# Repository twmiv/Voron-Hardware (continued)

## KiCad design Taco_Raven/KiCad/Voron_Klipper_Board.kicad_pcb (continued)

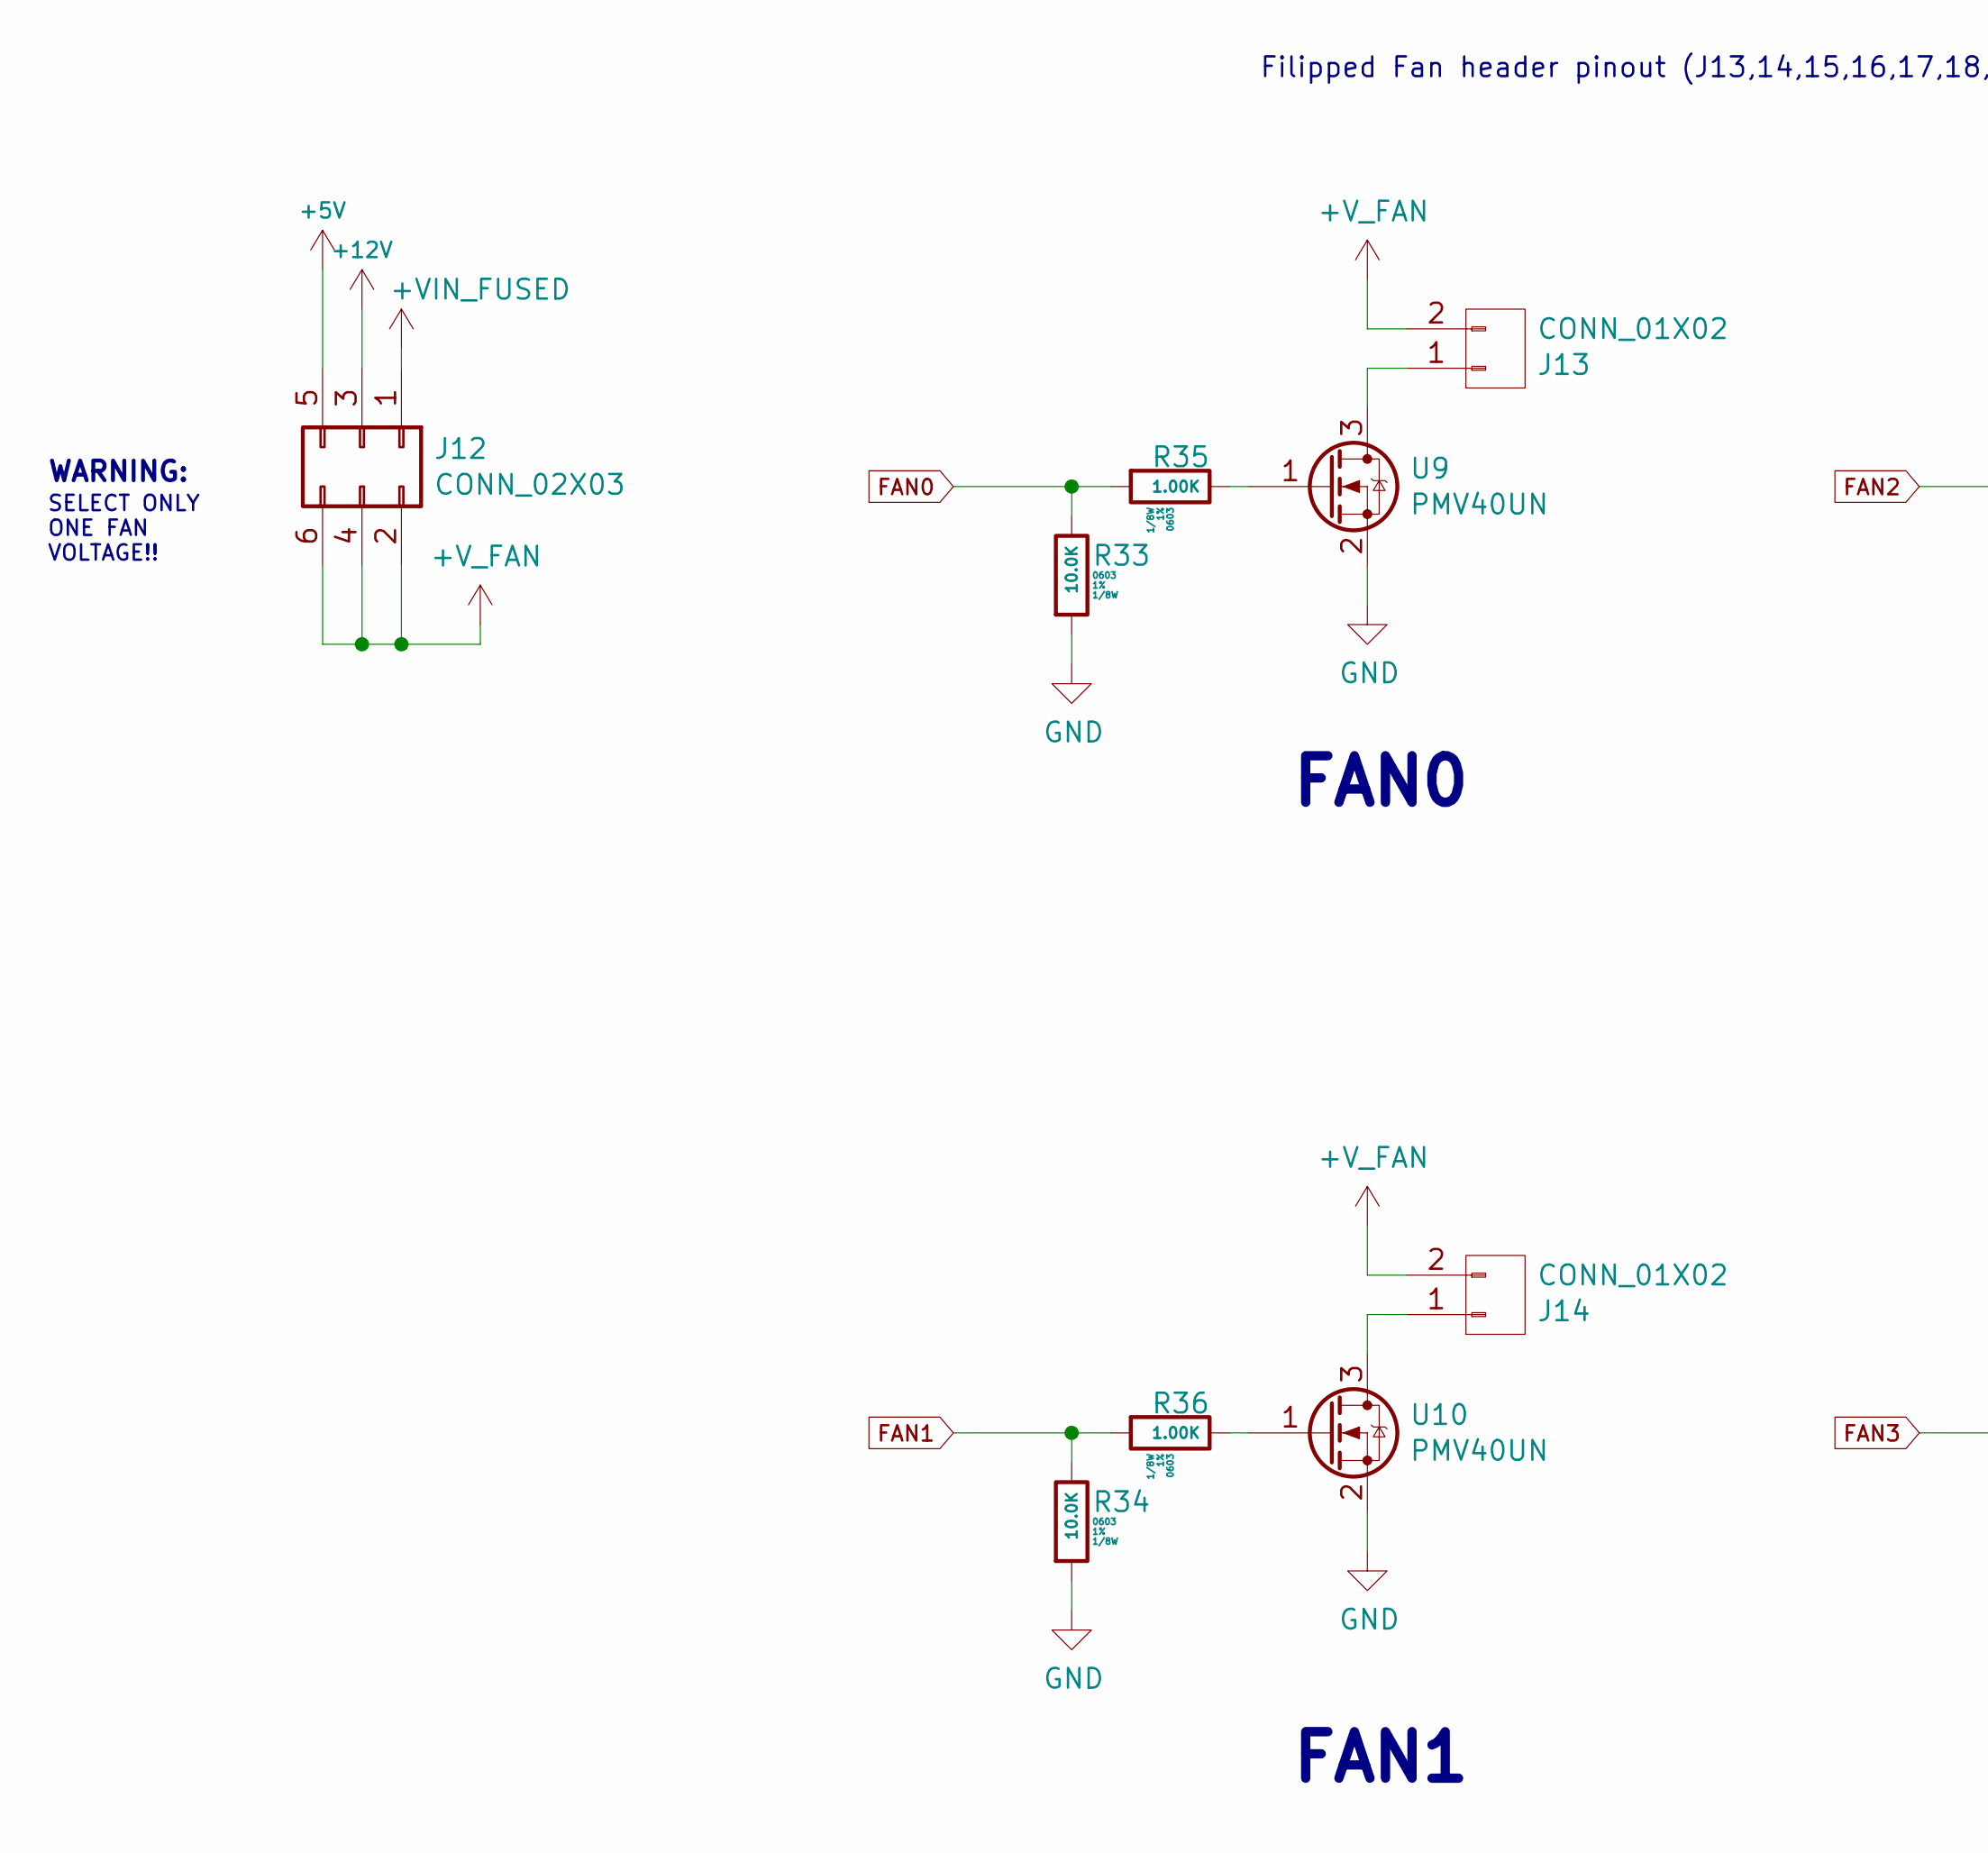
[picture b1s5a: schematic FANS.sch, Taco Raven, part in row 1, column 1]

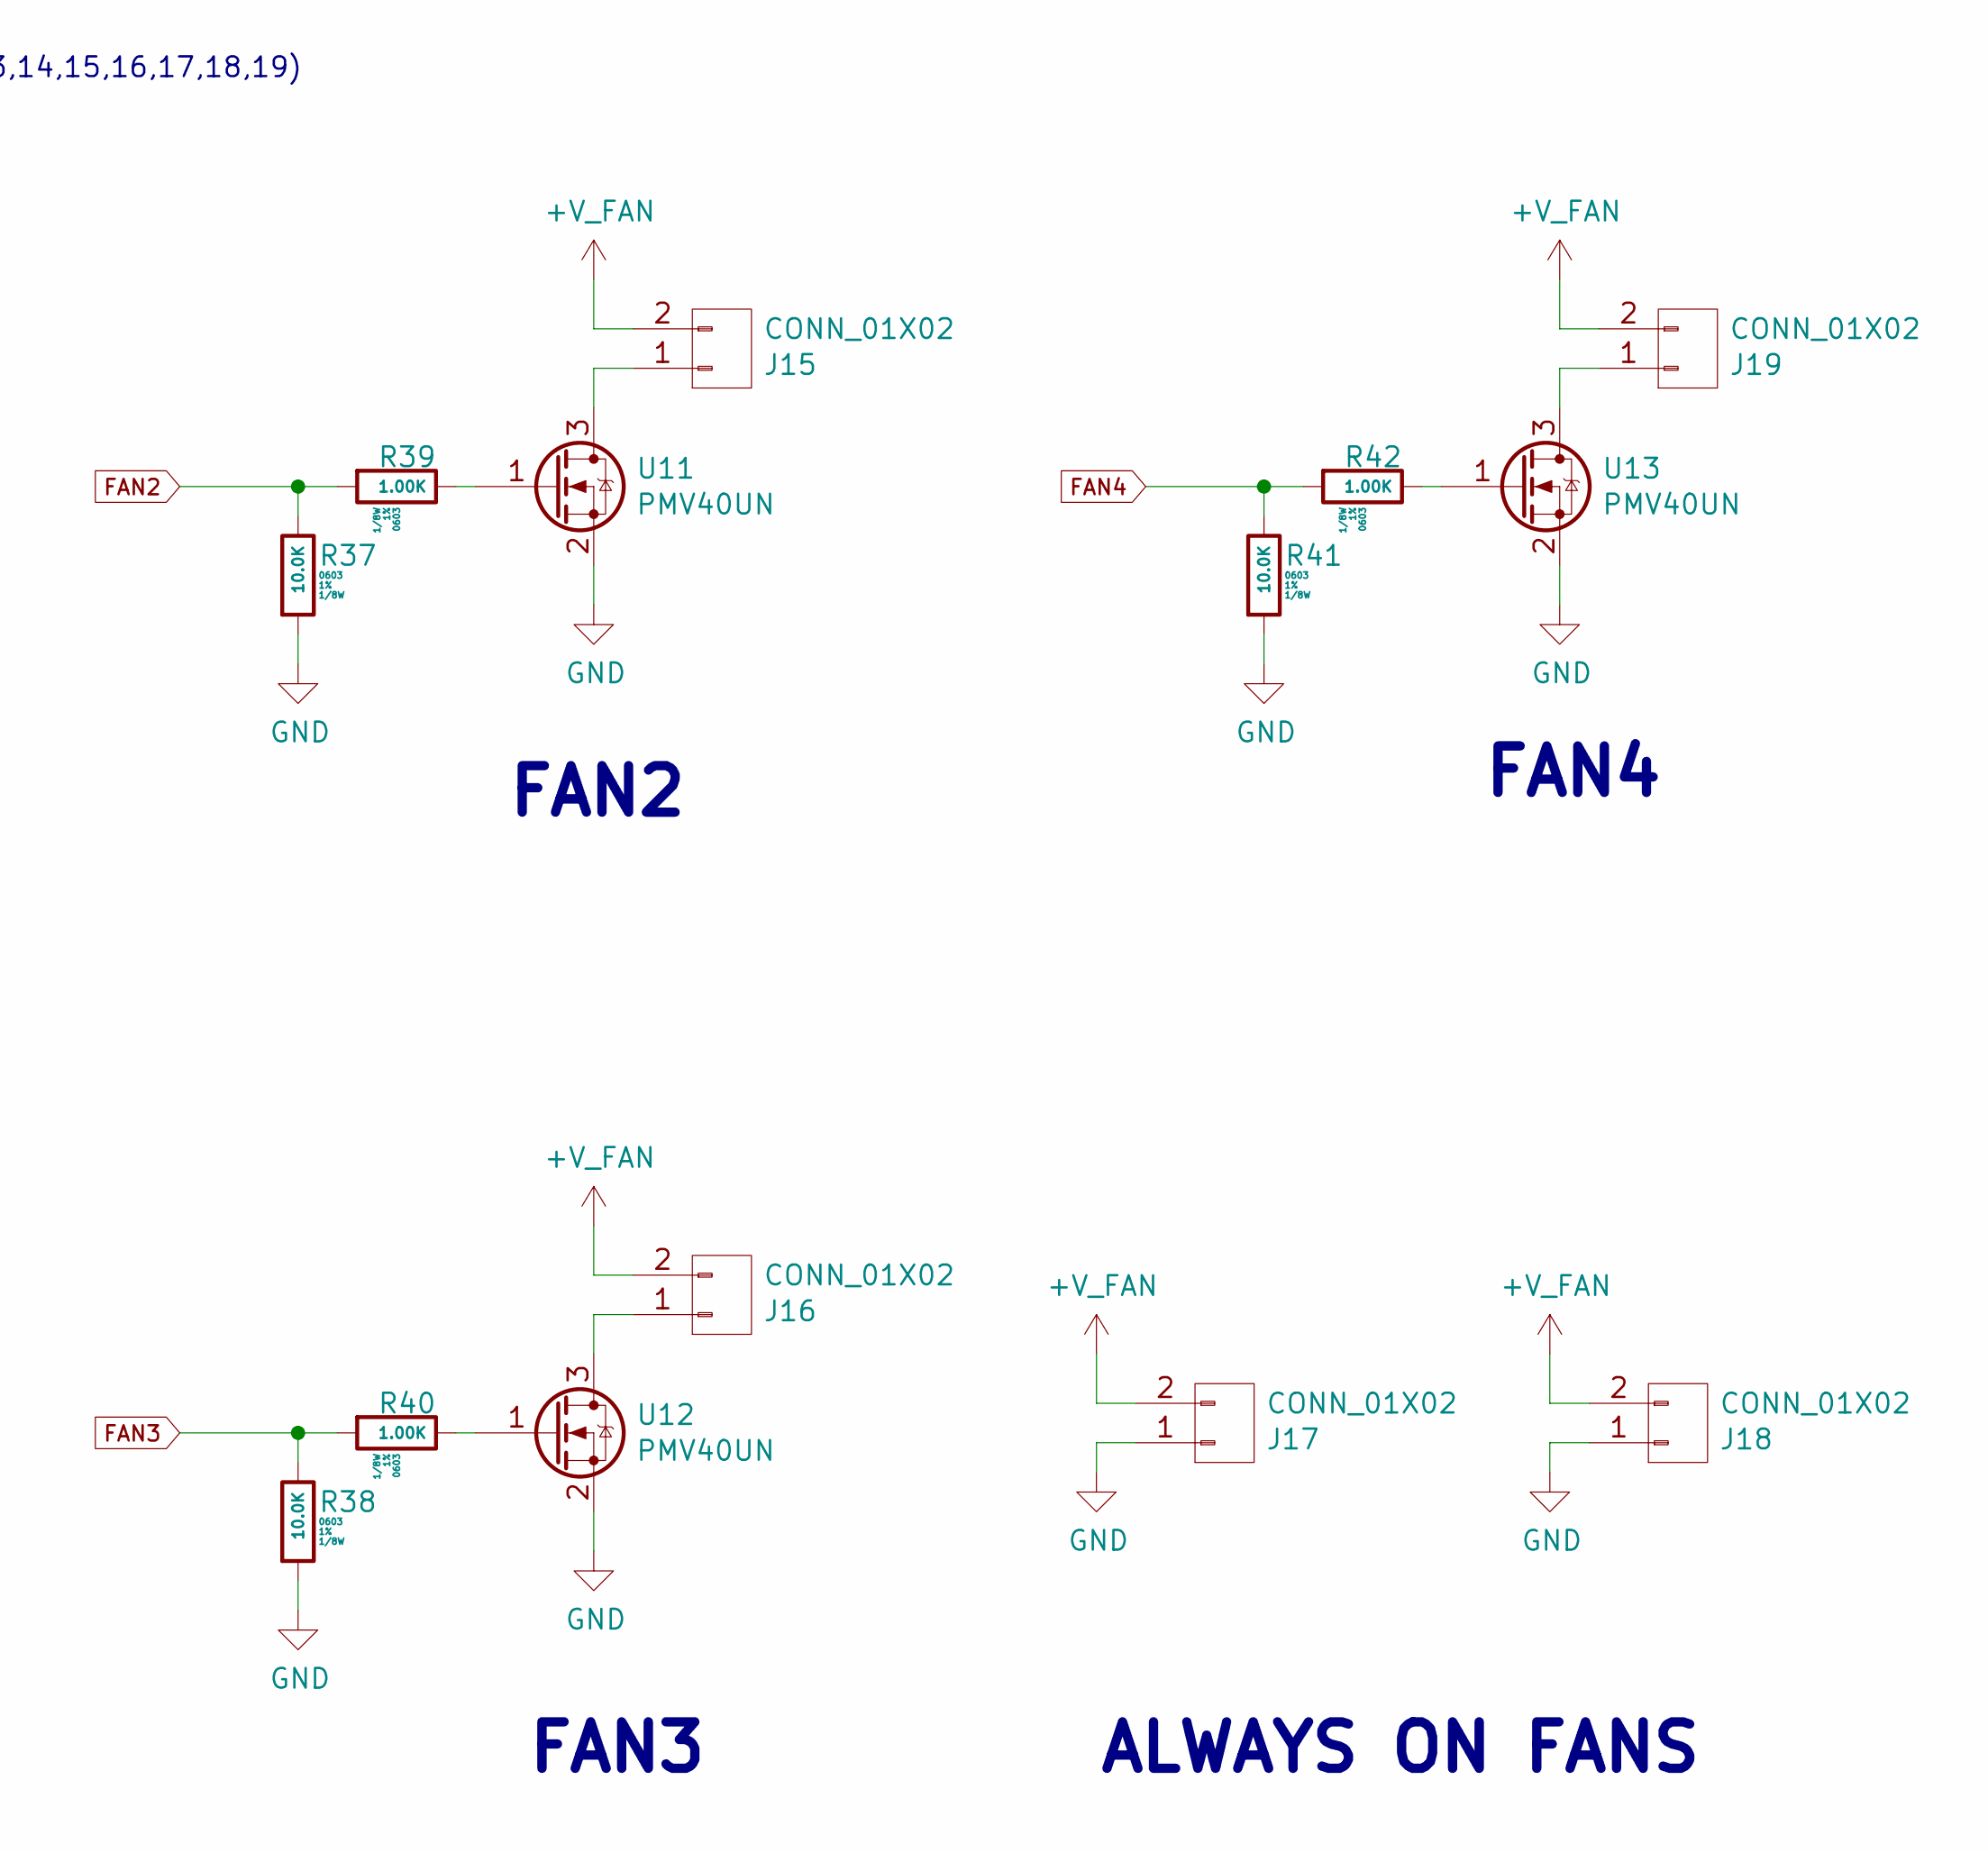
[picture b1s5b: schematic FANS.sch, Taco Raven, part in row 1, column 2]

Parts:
J12: CONN_02X03; PinHeader_2x03_P2.54mm_Vertical; MFG PN M20-9980346; Digikey P/N 952-2121-ND
J13, J14, J15, J16, J17, J18, J19: CONN_01X02; Molex_KK_1X2; MFG PN 22-23-2021; Digikey P/N WM4200-ND
R33, R34, R37, R38, R41: 10.0K; R_0603; Tolerance 1%; MFG PN RNCP0603FTD10K0; Digikey P/N RNCP0603FTD10K0CT-ND
R35, R36, R39, R40, R42: 1.00K; R_0603; Tolerance 1%; MFG PN RNCP0603FTD1K00; Digikey P/N RNCP0603FTD1K00CT-ND
U9, U10, U11, U12, U13: PMV40UN; SOT-23; MFG PN PMV40UN2R; Digikey P/N 1727-1900-1-ND

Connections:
+5V: J12.5; also elsewhere on the board
+12V: J12.3; also elsewhere on the board
+VIN_FUSED: J12.1; also elsewhere on the board
+V_FAN: J12.2, J12.4, J12.6, J13.2, J14.2, J15.2, J16.2, J17.2, J18.2, J19.2
FAN0: R33.1, R35.2; also elsewhere on the board
FAN1: R34.1, R36.2; also elsewhere on the board
FAN2: R37.1, R39.2; also elsewhere on the board
FAN3: R38.1, R40.2; also elsewhere on the board
FAN4: R41.1, R42.2; also elsewhere on the board
GND: J17.1, J18.1, R33.2, R34.2, R37.2, R38.2, R41.2, U9.2, U10.2, U11.2, U12.2, U13.2; also elsewhere on the board
unnamed: J13.1, U9.3
unnamed: J14.1, U10.3
unnamed: J15.1, U11.3
unnamed: J16.1, U12.3
unnamed: J19.1, U13.3
unnamed: R35.1, U9.1
unnamed: R36.1, U10.1
unnamed: R39.1, U11.1
unnamed: R40.1, U12.1
unnamed: R42.1, U13.1

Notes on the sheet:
FAN0
FAN1
FAN2
FAN3
FAN4
ALWAYS ON FANS
SELECT ONLY ONE FAN VOLTAGE!!
WARNING:
Filipped Fan header pinout (J13,14,15,16,17,18,19)

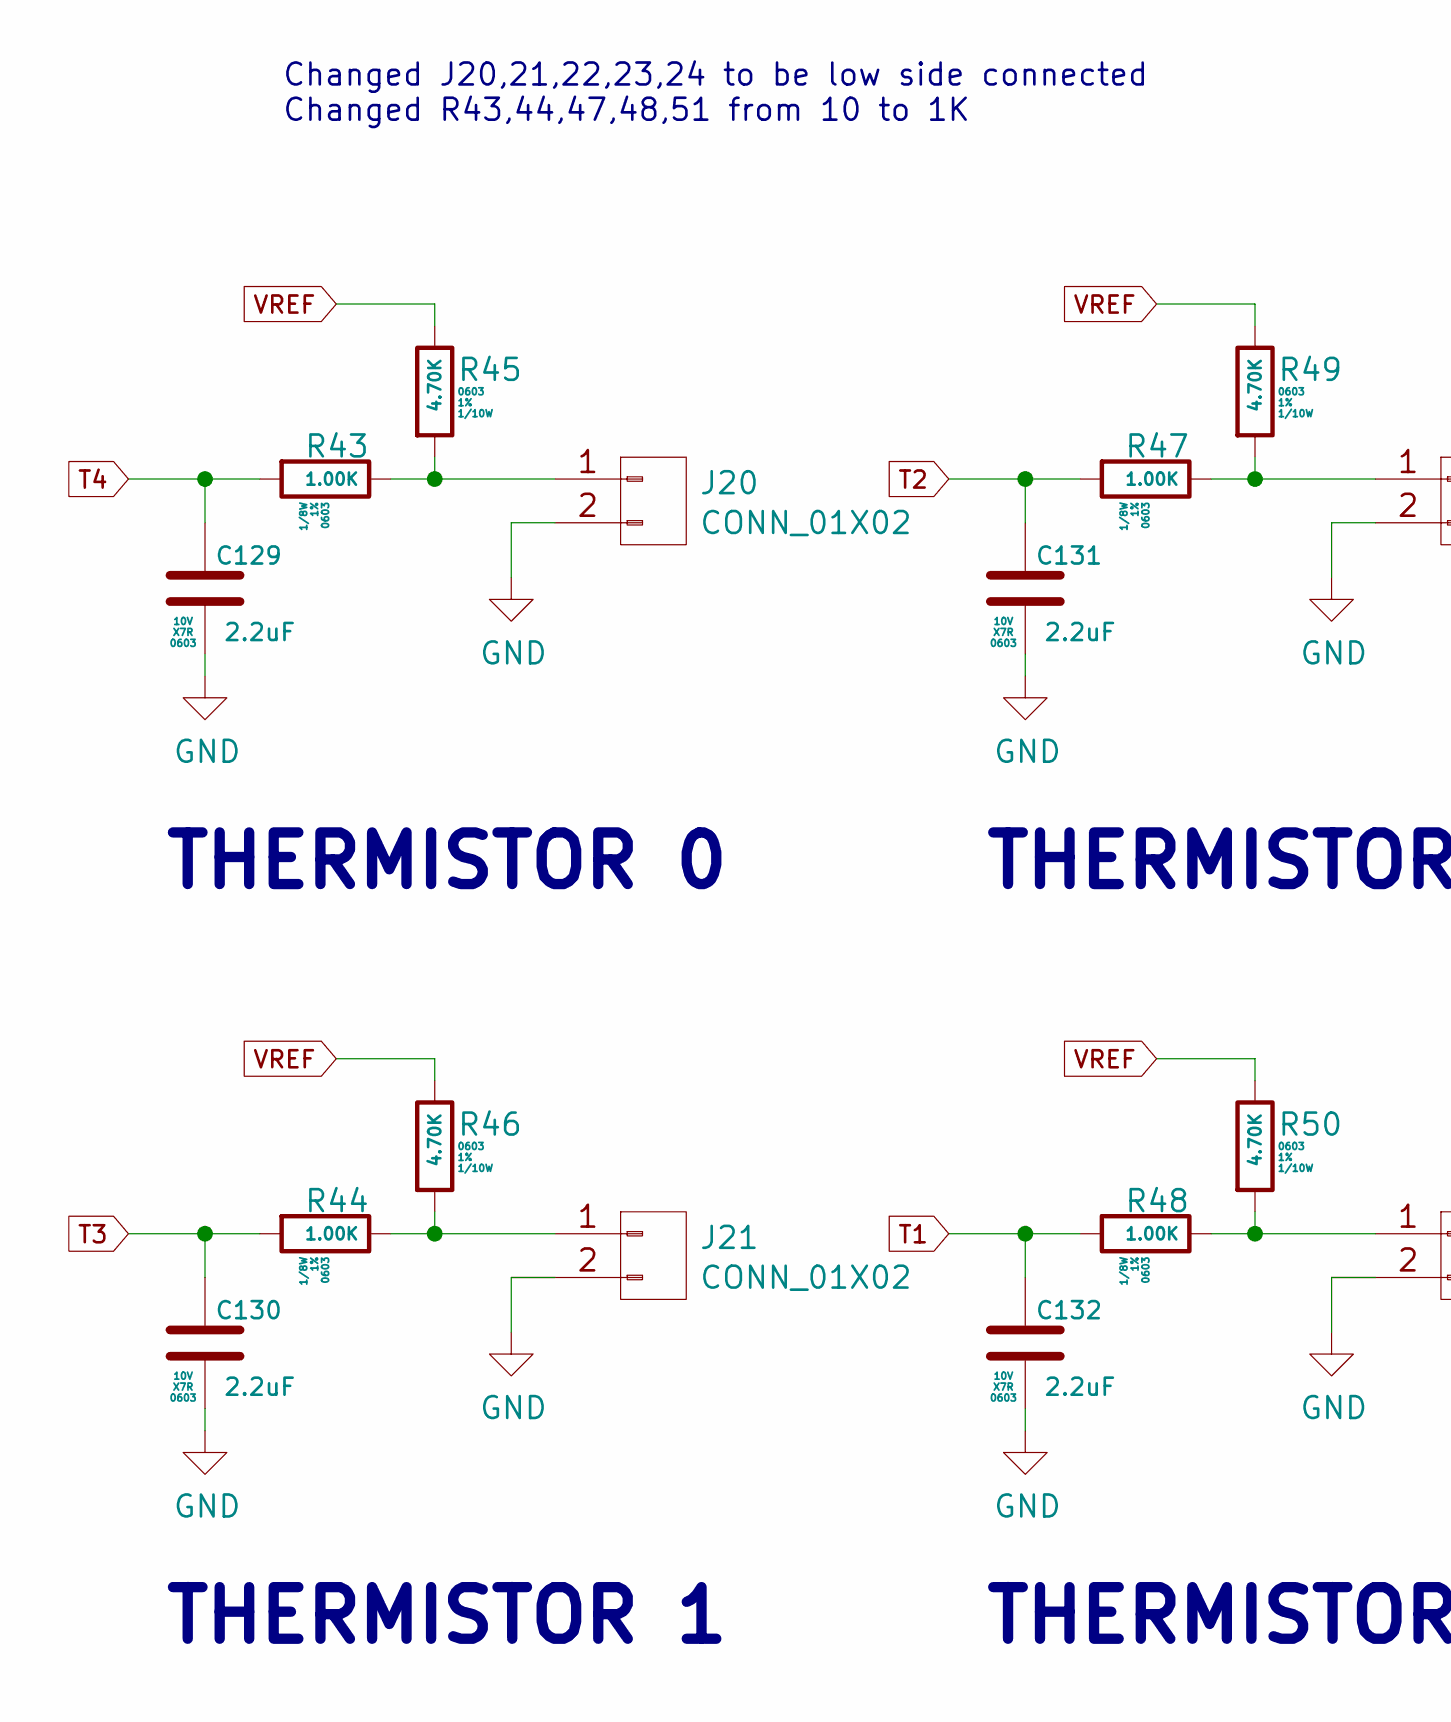
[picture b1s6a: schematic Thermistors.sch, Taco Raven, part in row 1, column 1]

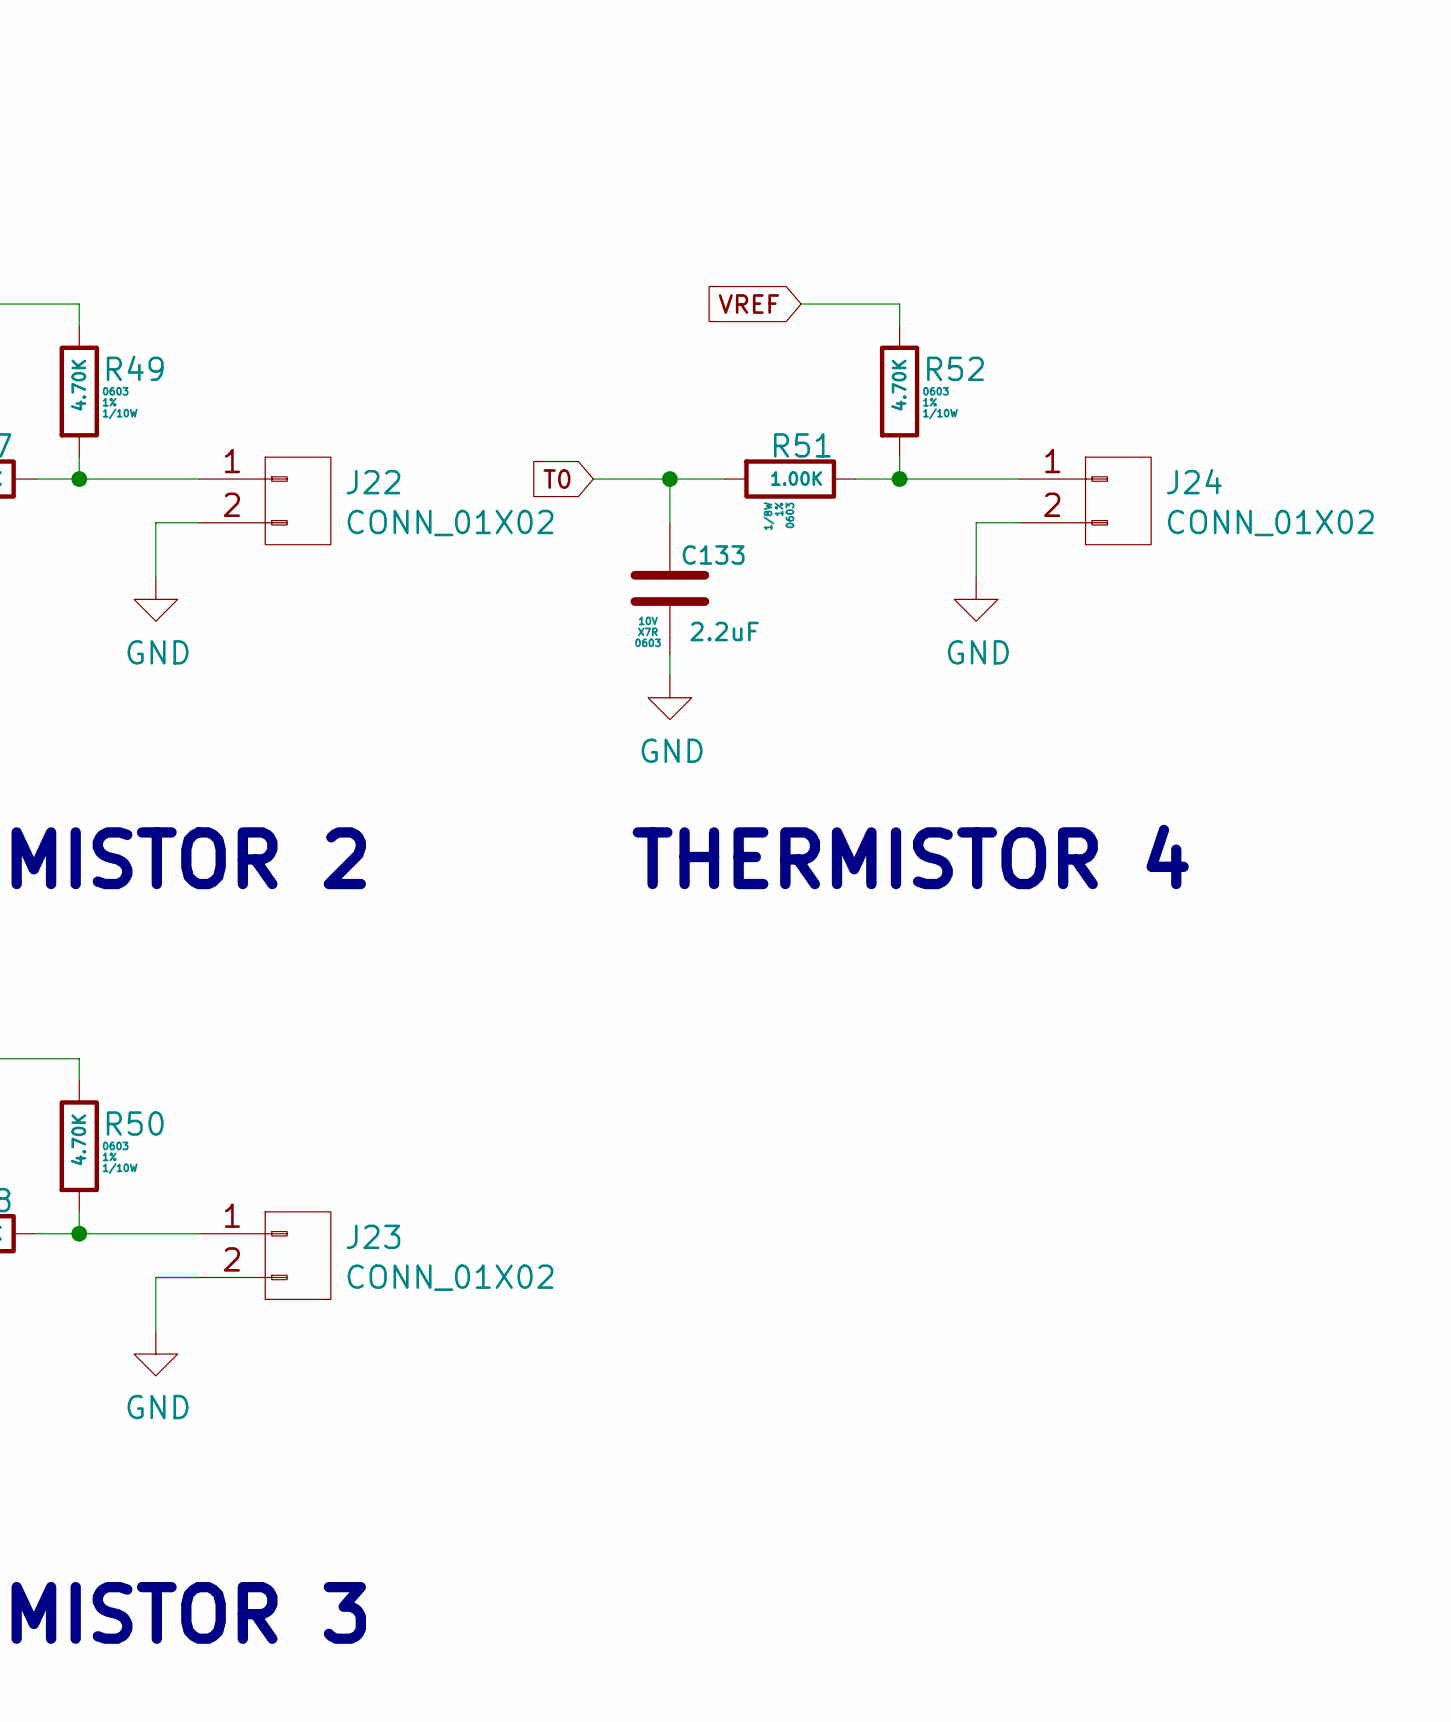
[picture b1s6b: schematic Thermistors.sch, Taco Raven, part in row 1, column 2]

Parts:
C129, C130, C131, C132, C133: 2.2uF; C_0603; Voltage 10V; MFG PN LMK107B7225KA-T; Digikey P/N 587-2983-1-ND
J20, J21, J22, J23, J24: CONN_01X02; Molex_KK_1X2; MFG PN 22-23-2021; Digikey P/N WM4200-ND
R43, R44, R47, R48, R51: 1.00K; R_0603; Tolerance 1%; MFG PN RNCP0603FTD1K00; Digikey P/N RNCP0603FTD1K00CT-ND
R45, R46, R49, R50, R52: 4.70K; R_0603; Tolerance 1%; MFG PN RC0603FR-074K7L; Digikey P/N 311-4.70KHRCT-ND

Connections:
GND: C129.1, C130.1, C131.1, C132.1, C133.1, J20.2, J21.2, J22.2, J23.2, J24.2; also elsewhere on the board
unnamed: J20.1, R43.1, R45.2
unnamed: J21.1, R44.1, R46.2
unnamed: J22.1, R47.1, R49.2
unnamed: J23.1, R48.1, R50.2
unnamed: J24.1, R51.1, R52.2
T0: C133.2, R51.2; also elsewhere on the board
T1: C132.2, R48.2; also elsewhere on the board
T2: C131.2, R47.2; also elsewhere on the board
T3: C130.2, R44.2; also elsewhere on the board
T4: C129.2, R43.2; also elsewhere on the board
VREF: R45.1, R46.1, R49.1, R50.1, R52.1; also elsewhere on the board

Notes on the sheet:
THERMISTOR 0
THERMISTOR 2
THERMISTOR 4
THERMISTOR 1
THERMISTOR 3
Changed J20,21,22,23,24 to be low side connected Changed R43,44,47,48,51 from 10 to 1K
